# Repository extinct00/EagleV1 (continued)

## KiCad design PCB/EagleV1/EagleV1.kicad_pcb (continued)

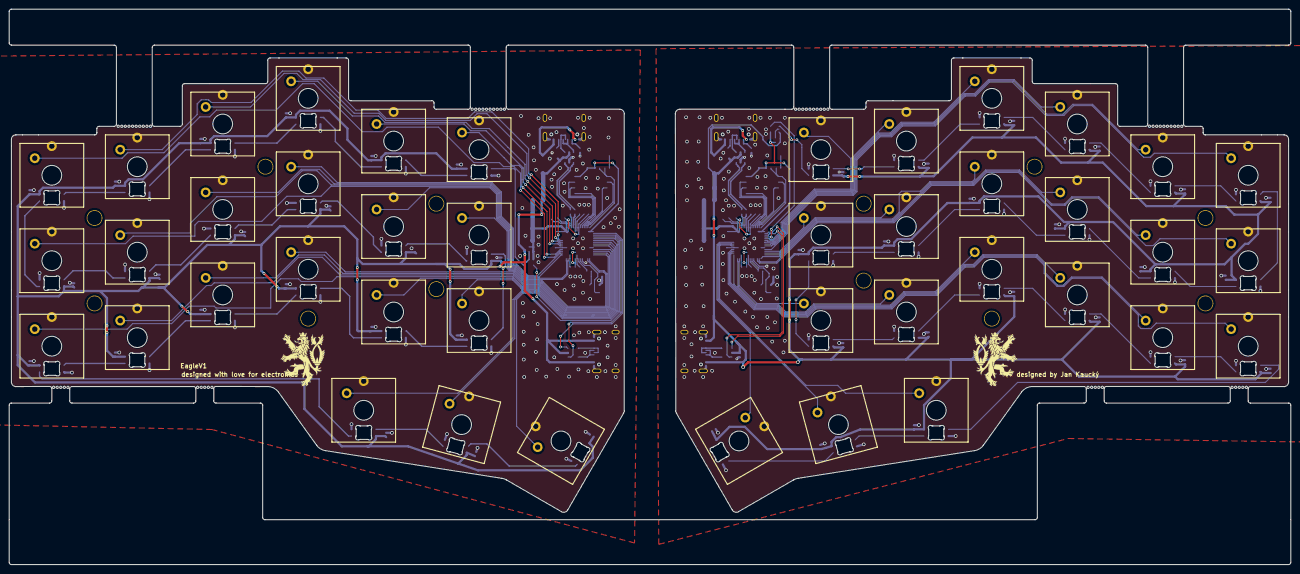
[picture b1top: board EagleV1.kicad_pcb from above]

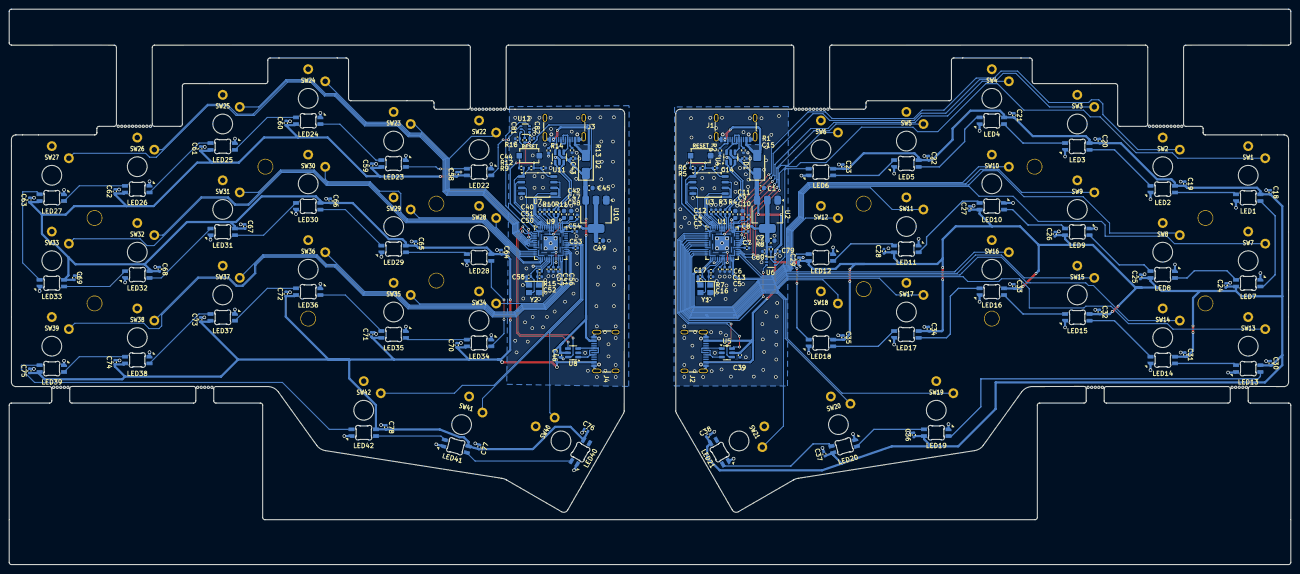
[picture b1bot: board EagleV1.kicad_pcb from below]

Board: 2 copper layers, 285.7 x 123.8 mm, 216 parts (162 on the bottom side), 142 nets.

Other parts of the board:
Mousbites 0.5mm NPTH with 0.3mm spacing, Mousbites 0.5mm NPTH with 0.3mm spacing#2, Mousbites 0.5mm NPTH with 0.3mm spacing#3, Mousbites 0.5mm NPTH with 0.3mm spacing#4, Mousbites 0.5mm NPTH with 0.3mm spacing#5, Mousbites 0.5mm NPTH with 0.3mm spacing#6, Mousbites 0.5mm NPTH with 0.3mm spacing#7, Mousbites 0.5mm NPTH with 0.3mm spacing#8, Mousbites 0.5mm NPTH with 0.3mm spacing#9, Mousbites 0.5mm NPTH with 0.3mm spacing#10, Mousbites 0.5mm NPTH with 0.3mm spacing#11, Mousbites 0.5mm NPTH with 0.3mm spacing#12: Corne_mousebites

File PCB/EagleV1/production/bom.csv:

Designator,Footprint,Quantity,Value,LCSC Part #
"C1, C11, C2, C42, C45, C47, C49, C9",0603,8,1u,
"C10, C12, C13, C14, C15, C18, C19, C20, C21, C22, C23, C24, C25, C26, C27, C28, C29, C3, C30, C31, C32, C33, C34, C35, C36, C37, C38, C39, C4, C40, C41, C43, C44, C46, C48, C5, C50, C51, C53, C54, C56, C57, C58, C59, C6, C60, C61, C62, C63, C64, C65, C66, C67, C68, C69, C7, C70, C71, C72, C73, C74, C75, C76, C77, C78, C79, C8, C80, C81, C82",0402,70,100n,
"C16, C17, C52, C55",0402,4,15p,
"D1, D2",D_SMA,2,SS14,
"J1, J2, J3, J4",USB_C_Receptacle_G-Switch_GT-USB-7010ASV,4,USB_C_Receptacle_USB2.0_16P,
"LED1, LED10, LED11, LED12, LED13, LED14, LED15, LED16, LED17, LED18, LED19, LED2, LED20, LED21, LED22, LED23, LED24, LED25, LED26, LED27, LED28, LED29, LED3, LED30, LED31, LED32, LED33, LED34, LED35, LED36, LED37, LED38, LED39, LED4, LED40, LED41, LED42, LED5, LED6, LED7, LED8, LED9",LED_6028R,42,SK6812MINI-E,
"MOUSBITES 0.5MM NPTH WITH 0.3MM SPACING_12, MOUSBITES 0.5MM NPTH WITH 0.3MM SPACING_11, MOUSBITES 0.5MM NPTH WITH 0.3MM SPACING_10, MOUSBITES 0.5MM NPTH WITH 0.3MM SPACING_9, MOUSBITES 0.5MM NPTH WITH 0.3MM SPACING_8, MOUSBITES 0.5MM NPTH WITH 0.3MM SPACING_7, MOUSBITES 0.5MM NPTH WITH 0.3MM SPACING_6, MOUSBITES 0.5MM NPTH WITH 0.3MM SPACING_5, MOUSBITES 0.5MM NPTH WITH 0.3MM SPACING_4, MOUSBITES 0.5MM NPTH WITH 0.3MM SPACING_3, MOUSBITES 0.5MM NPTH WITH 0.3MM SPACING_2, MOUSBITES 0.5MM NPTH WITH 0.3MM SPACING",Corne_mousebites,12,Corne_mousebites,
"R1, R13, R14, R2",0402,4,5.1k,
"R10, R11, R3, R4",0402,4,27,
"R12, R16, R5, R8",0402,4,10k,
"R15, R6, R7, R9",0402,4,1k,
"SW1, SW10, SW11, SW12, SW13, SW14, SW15, SW16, SW17, SW18, SW19, SW2, SW20, SW21, SW22, SW23, SW24, SW25, SW26, SW27, SW28, SW29, SW3, SW30, SW31, SW32, SW33, SW34, SW35, SW36, SW37, SW38, SW39, SW4, SW40, SW41, SW42, SW5, SW6, SW7, SW8, SW9",SW_Redragon_LowProfile_PCB_1.00u,42,SW_Push,
"SW98, SW99",SW_TS-1088_XNP,2,TS-1088-AR02016,
"U1, U9",QFN-56-1EP_7x7mm_P0.4mm_EP3.2x3.2mm,2,RP2040,
"U10, U2",SOT-223-3_TabPin2,2,TLV1117-33,
"U11, U4, U5, U8",SOT-23-6,4,USBLC6-2SC6,
"U12, U6",SOT-363_SC-70-6,2,SN74LVC1T45DCK,
"U3, U7",SOIC-8_5.23x5.23mm_P1.27mm,2,W25Q128JVS,
Y1,Crystal_SMD_3225-4Pin_3.2x2.5mm,1,Crystal_GND24,
Y2,Crystal_SMD_3225-4Pin_3.2x2.5mm,1,Crystal_GNDB24,

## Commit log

2025-02-02 created a repo
2025-02-02 added a v2 plate
2025-02-02 created a 3d model for v2 plate
2025-02-02 created a kicad project
2025-02-04 creating a schematic
2025-02-10 finished schematic
2025-02-13 started keyboard rounting
2025-02-15 finished pcb layout
2025-02-16 routed all the tracks and smds
2025-02-16 Finished layout, both halves
2025-02-16 readme update
2025-02-19 finished the PCB layout, exported gerbers
2025-02-20 edited LED caps via placement and added some finishing touches
2025-02-25 V1 now finalized, meaby will play a little with the silkscreen
